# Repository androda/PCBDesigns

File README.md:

# PCBDesigns
 PCB Designs By Androda

 Note the Non-Commercial license.  You are encouraged to make these boards for yourself (personal use) or as gifts for others (provided that they are true gifts, and not being used to trade for something).  If you would like to license these designs for commercial sale, please contact me and we can work out a license agreement: https://androda.work/about/

# BlueSCSI
 These PCBs are intended to be used with the BlueSCSI project, found here: https://github.com/erichelgeson/BlueSCSI

# Newton
 PCBs for the Apple Newton

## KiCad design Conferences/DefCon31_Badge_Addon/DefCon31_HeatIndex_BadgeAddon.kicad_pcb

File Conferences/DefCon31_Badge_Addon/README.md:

# DefCon 31 Badge Addon
 This was my quick attempt to get something ready for DefCon 31.  The process of getting the PCB outline imported to KiCAD was not easy.

# What does it do?
 It's a "[Heat Index](https://www.weather.gov/safety/heat-index)" calculator and indicator.  The Heat Index is a way to calculate the temperature it "feels like" based on the combination of temperature and humidity in your current environment.
 
 The LED flashes about once per second (internal oscillators being as they are), with a color based on the calculated Heat Index.  Note that these temperatures are all in Fahrenheit.  Blue for < 80 degrees, Green for 81 to 90 degrees, Yellow for 91 to 104 degrees, Red for 105 to 125 degrees, and Purple for anything above that.

 The "yellow" color doesn't work very well due to lack of time in figuring out good PWM mixing values.  I use the term PWM loosely here, it's basically manual PWM due to issues with getting hardware PWM working properly
 
 Battery life isn't great, I was unable to get STOP mode with RTC wake working properly, even with a supposed "template" for doing so from the manufacturer.  Instead it uses SLEEP mode with a hardware timer wakeup, and the battery lasts about 12 hours.

 It's also a breakout board in that I routed all the additional pins to standard 2.54mm header strip positions.  So go ahead and reflash this as something more useful later on.  :)
 
# Is it useful?
 Kind of.  Maybe.  Was a good project for learning the [STM32Duino](https://github.com/stm32duino/Arduino_Core_STM32) framework, and for discovering that basically nothing in Arduino is as easy as it sounds when trying to use hardware peripherals.
 
# What chips are those?
* SHTC3 Temperature and Humidity Sensor
* STM32F030 Microcontroller
* Osram LRTBR48G LED
 
# License
 Licensed Creative Commons Attribution-NonCommercial-ShareAlike 4.0.
 https://creativecommons.org/licenses/by-nc-sa/4.0/
 https://creativecommons.org/licenses/by-nc-sa/4.0/deed.fr

Obligatory PCB Image:

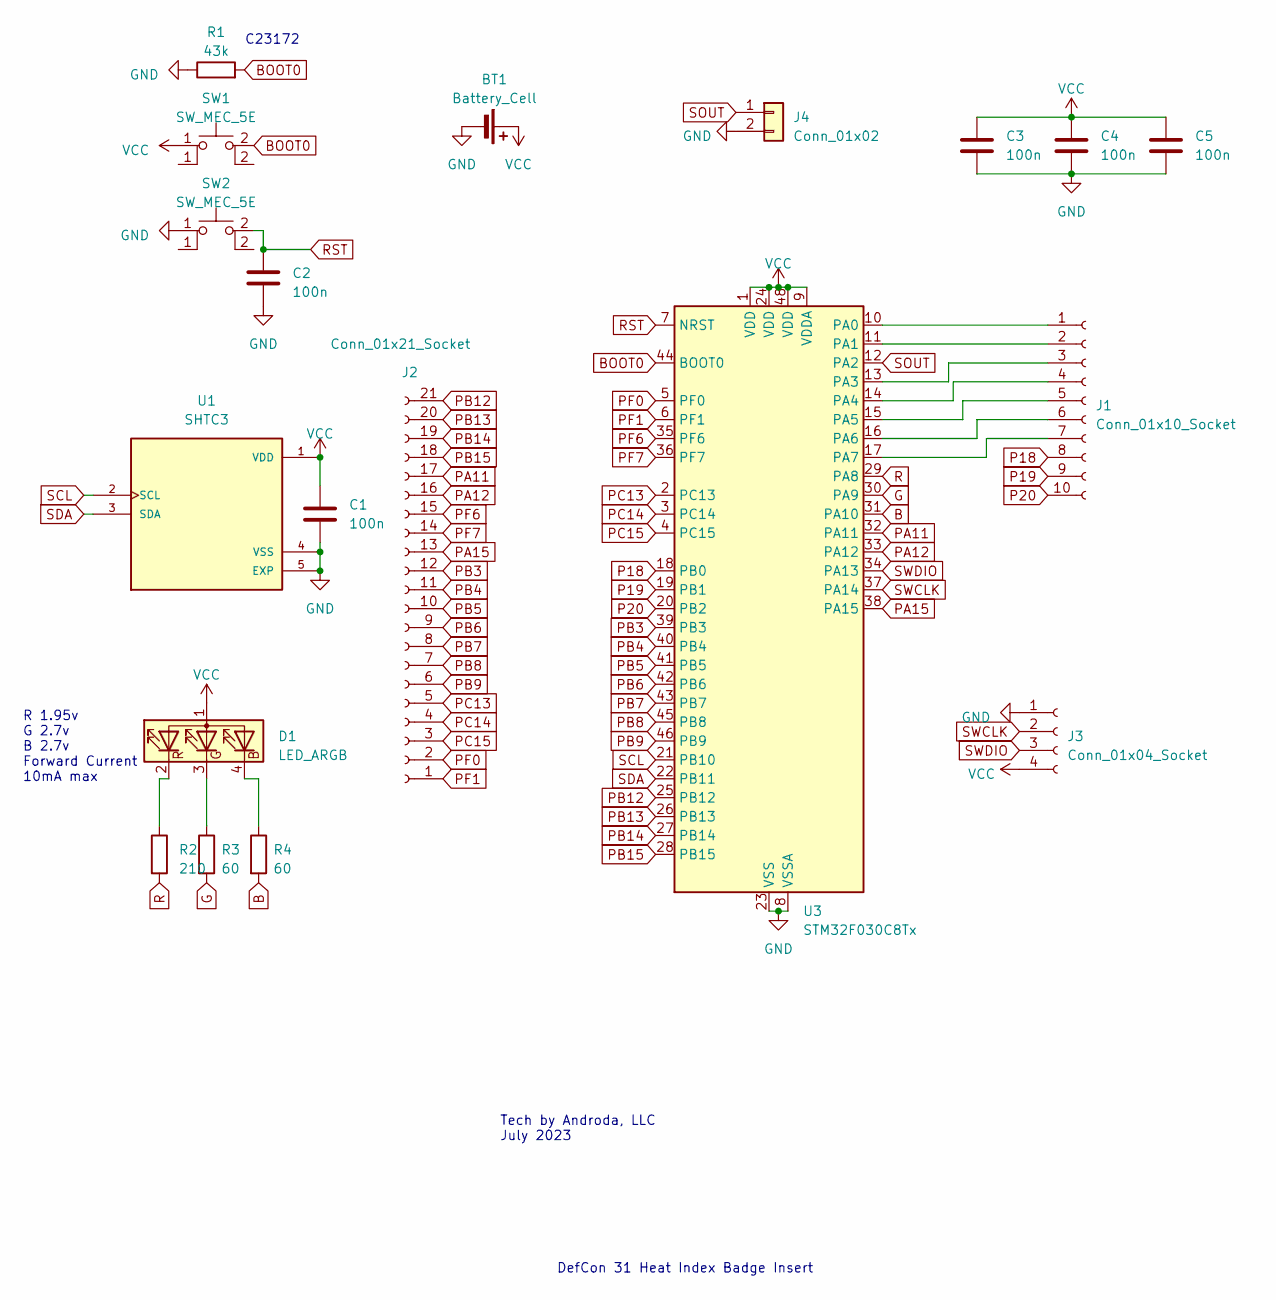
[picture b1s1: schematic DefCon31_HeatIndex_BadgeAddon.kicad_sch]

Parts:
BT1: Battery_Cell; CR1632
C1, C2, C3, C4, C5: 100n; C_0603_1608Metric
D1: LED_ARGB; LRTB_R48G
J1: Conn_01x10_Socket; PinSocket_1x10_P2.54mm_Vertical
J2: Conn_01x21_Socket; PinSocket_1x21_P2.54mm_Vertical
J3: Conn_01x04_Socket; PinSocket_1x04_P2.54mm_Vertical
J4: Conn_01x02; PinSocket_1x02_P2.54mm_Vertical
R1: 43k; R_0603_1608Metric
R2: 210; R_0603_1608Metric
R3, R4: 60; R_0603_1608Metric
SW1, SW2: SW_MEC_5E; TS-1187A-B-A-B
U1: SHTC3; SON100P200X200X80-5N; PARTREV 3
U3: STM32F030C8Tx; LQFP-48_7x7mm_P0.5mm

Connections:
B: R4.2, U3.31 (PA10)
BOOT0: R1.2, SW1.2, U3.44 (BOOT0)
G: R3.2, U3.30 (PA9)
GND: BT1.2 (-), C1.2, C2.2, C3.2, C4.2, C5.2, J3.1, J4.2, R1.1, SW2.1, U1.4 (VSS), U1.5 (EXP), U3.8 (VSSA), U3.23 (VSS), U3.47 (VSS)
unnamed: D1.4 (BK), R4.1
unnamed: D1.3 (GK), R3.1
unnamed: D1.2 (RK), R2.1
unnamed: J1.1, U3.10 (PA0)
unnamed: J1.2, U3.11 (PA1)
unnamed: J1.3, U3.13 (PA3)
unnamed: J1.4, U3.14 (PA4)
unnamed: J1.5, U3.15 (PA5)
unnamed: J1.6, U3.16 (PA6)
unnamed: J1.7, U3.17 (PA7)
P18: J1.8, U3.18 (PB0)
P19: J1.9, U3.19 (PB1)
P20: J1.10, U3.20 (PB2)
PA11: J2.17, U3.32 (PA11)
PA12: J2.16, U3.33 (PA12)
PA15: J2.13, U3.38 (PA15)
PB3: J2.12, U3.39 (PB3)
PB4: J2.11, U3.40 (PB4)
PB5: J2.10, U3.41 (PB5)
PB6: J2.9, U3.42 (PB6)
PB7: J2.8, U3.43 (PB7)
PB8: J2.7, U3.45 (PB8)
PB9: J2.6, U3.46 (PB9)
PB12: J2.21, U3.25 (PB12)
PB13: J2.20, U3.26 (PB13)
PB14: J2.19, U3.27 (PB14)
PB15: J2.18, U3.28 (PB15)
PC13: J2.5, U3.2 (PC13)
PC14: J2.4, U3.3 (PC14)
PC15: J2.3, U3.4 (PC15)
PF0: J2.2, U3.5 (PF0)
PF1: J2.1, U3.6 (PF1)
PF6: J2.15, U3.35 (PF6)
PF7: J2.14, U3.36 (PF7)
R: R2.2, U3.29 (PA8)
RST: C2.1, SW2.2, U3.7 (NRST)
SCL: U1.2 (SCL), U3.21 (PB10)
SDA: U1.3 (SDA), U3.22 (PB11)
SOUT: J4.1, U3.12 (PA2)
SWCLK: J3.2, U3.37 (PA14)
SWDIO: J3.3, U3.34 (PA13)
VCC: BT1.1 (+), C1.1, C3.1, C4.1, C5.1, D1.1 (A), J3.4, SW1.1, U1.1 (VDD), U3.1 (VDD), U3.9 (VDDA), U3.24 (VDD), U3.48 (VDD)

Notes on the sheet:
R 1.95v G 2.7v B 2.7v Forward Current 10mA max
DefCon 31 Heat Index Badge Insert
Tech by Androda, LLC July 2023
C23172

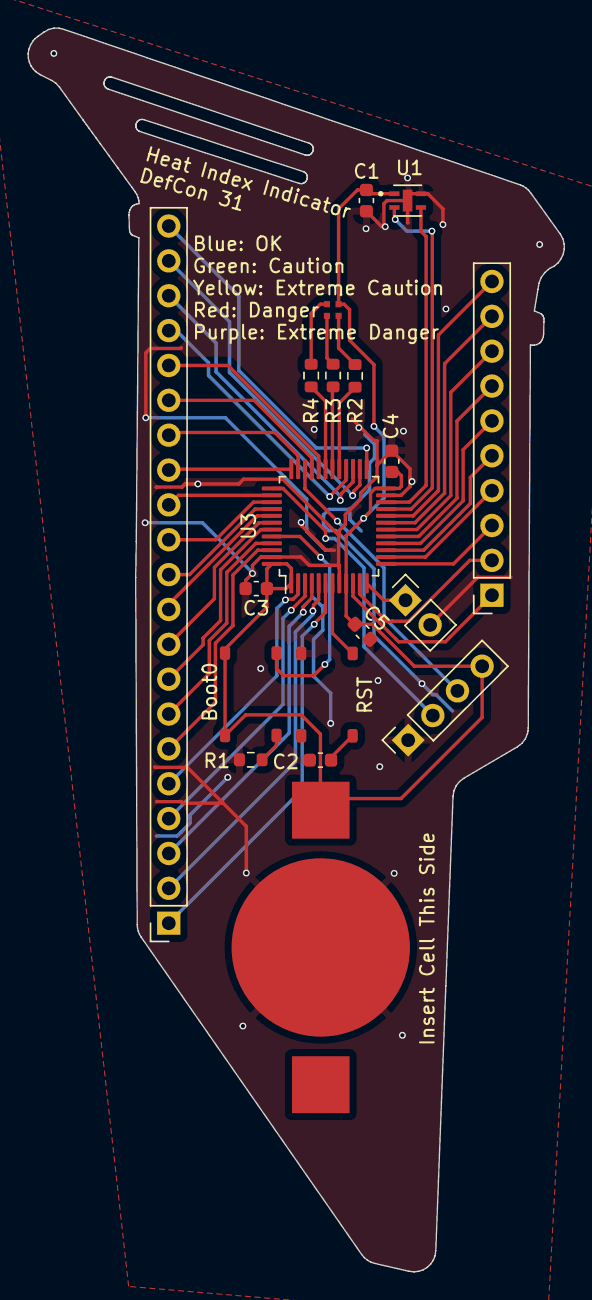
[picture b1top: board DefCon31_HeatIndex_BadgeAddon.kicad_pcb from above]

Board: 2 copper layers, 39.1 x 90.6 mm, 19 parts (0 on the bottom side), 46 nets.

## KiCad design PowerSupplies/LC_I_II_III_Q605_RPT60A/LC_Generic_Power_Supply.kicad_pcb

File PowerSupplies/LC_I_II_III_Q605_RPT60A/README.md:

Licensed Creative Commons Attribution-NonCommercial-ShareAlike 4.0.
https://creativecommons.org/licenses/by-nc-sa/4.0/
https://creativecommons.org/licenses/by-nc-sa/4.0/deed.fr

This is a power supply replacement design for the LC I through III series plus Q605.  It uses a MeanWell RPT-60A power supply that provides the usual 12/5/-5, with this PCB being effectively a protection board to try and keep your vintage system safe in case of power surges or regulation failures.  It's a working design, just move over the power output cable from the original supply (which could need extending).

This design uses the output pads layout from the "MacTX LC" which was released to the public domain.  Other than that it's an original design.

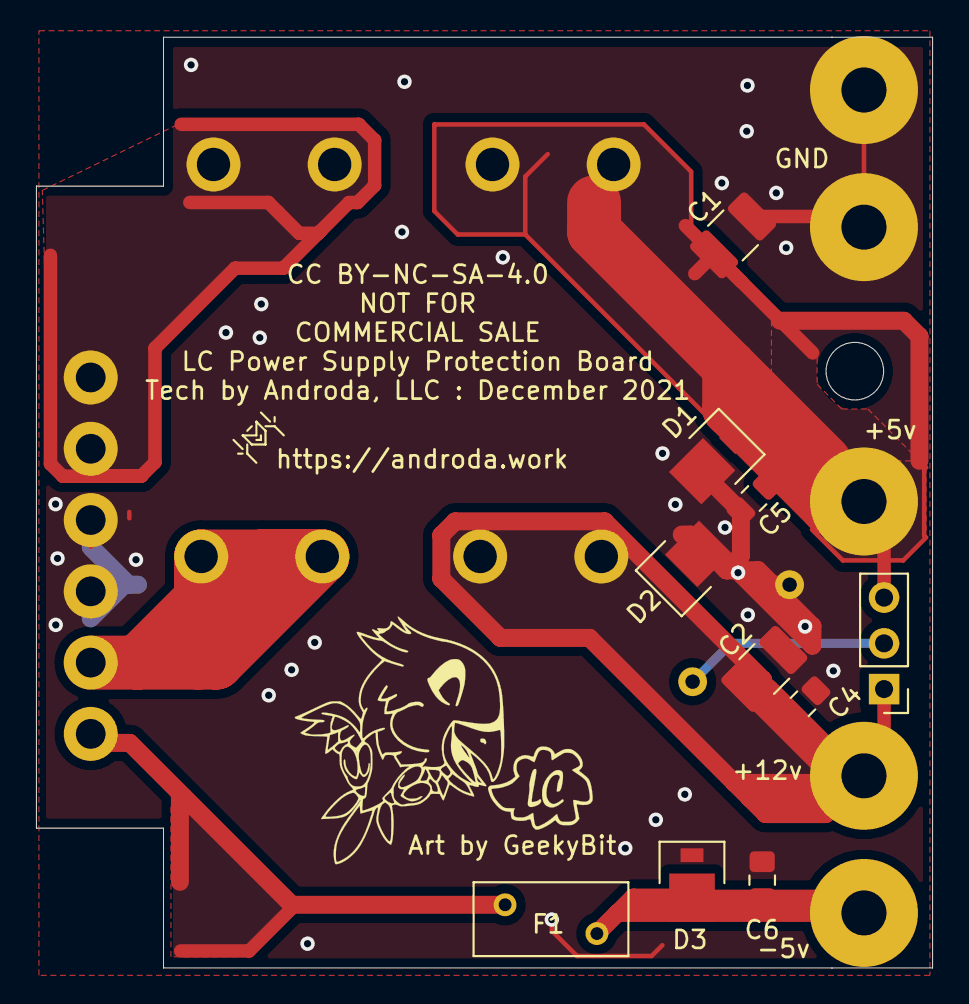
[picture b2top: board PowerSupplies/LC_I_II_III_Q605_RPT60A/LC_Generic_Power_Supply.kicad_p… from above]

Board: 2 copper layers, 49.8 x 51.7 mm, 17 parts (1 on the bottom side), 8 nets.

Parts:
C1, C2: 47uF 10v; C_1210_3225Metric_Pad1.42x2.65mm_HandSolder
C4, C5, C6: C; C_0805_2012Metric_Pad1.15x1.40mm_HandSolder
D1, D3: 5.6v Zener; DO-220AA
D2: 12.6v Zener; DO-220AA
F1: Polyfuse; Fuse_BelFuse_0ZRE0005FF_L8.3mm_W3.8mm
FH1, FH2: FuseHolders_FC-202-24
H2: MountingHole; MountingHole_3.2mm_M3
J1: RPT-60-6Pin-Out
J3: Conn_01x03_Male; PinHeader_1x03_P2.54mm_Vertical
J6: Conn_01x05_Male; LC_MACAA_Pads
R1: R; R_Axial_DIN0207_L6.3mm_D2.5mm_P7.62mm_Horizontal
Ref**: Val**; MACAAAAAAAAAA_1812

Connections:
+5V: C1.1, C5.1, D1.1, FH2.2, J3.3, J6.3
+12V: C2.1, C4.1, D2.1, FH1.2, J3.1, J6.4
-5V: C6.1, D3.2, F1.1, J6.5
GND: C1.2, C2.2, C4.2, C5.2, C6.2, D1.2, D2.2, D3.1, J1.3, J1.4, J6.1, J6.2, R1.2
unnamed: F1.2, J1.6
unnamed: FH1.1, J1.5
unnamed: FH2.1, J1.1, J1.2
unnamed: J3.2, R1.1

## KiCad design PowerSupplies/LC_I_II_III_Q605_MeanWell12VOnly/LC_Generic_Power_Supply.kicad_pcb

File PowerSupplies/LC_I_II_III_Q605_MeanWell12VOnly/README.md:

Licensed Creative Commons Attribution-NonCommercial-ShareAlike 4.0.
https://creativecommons.org/licenses/by-nc-sa/4.0/
https://creativecommons.org/licenses/by-nc-sa/4.0/deed.fr

This is a power supply replacement design for the LC I through III series plus Q605.  It uses a 12v MeanWell power supply which is then down-converted as necessary to provide the usual 12/5/-5 supply.  It's a working design, but too big of a pain to try and sell given the very small working area and cost which approaches a new old stock power supply replacement.  In the future when LC power supplies are entirely unavailble it might have some use.

This design uses the output pads layout from the "MacTX LC" which was released to the public domain.  Other than that it's an original design.

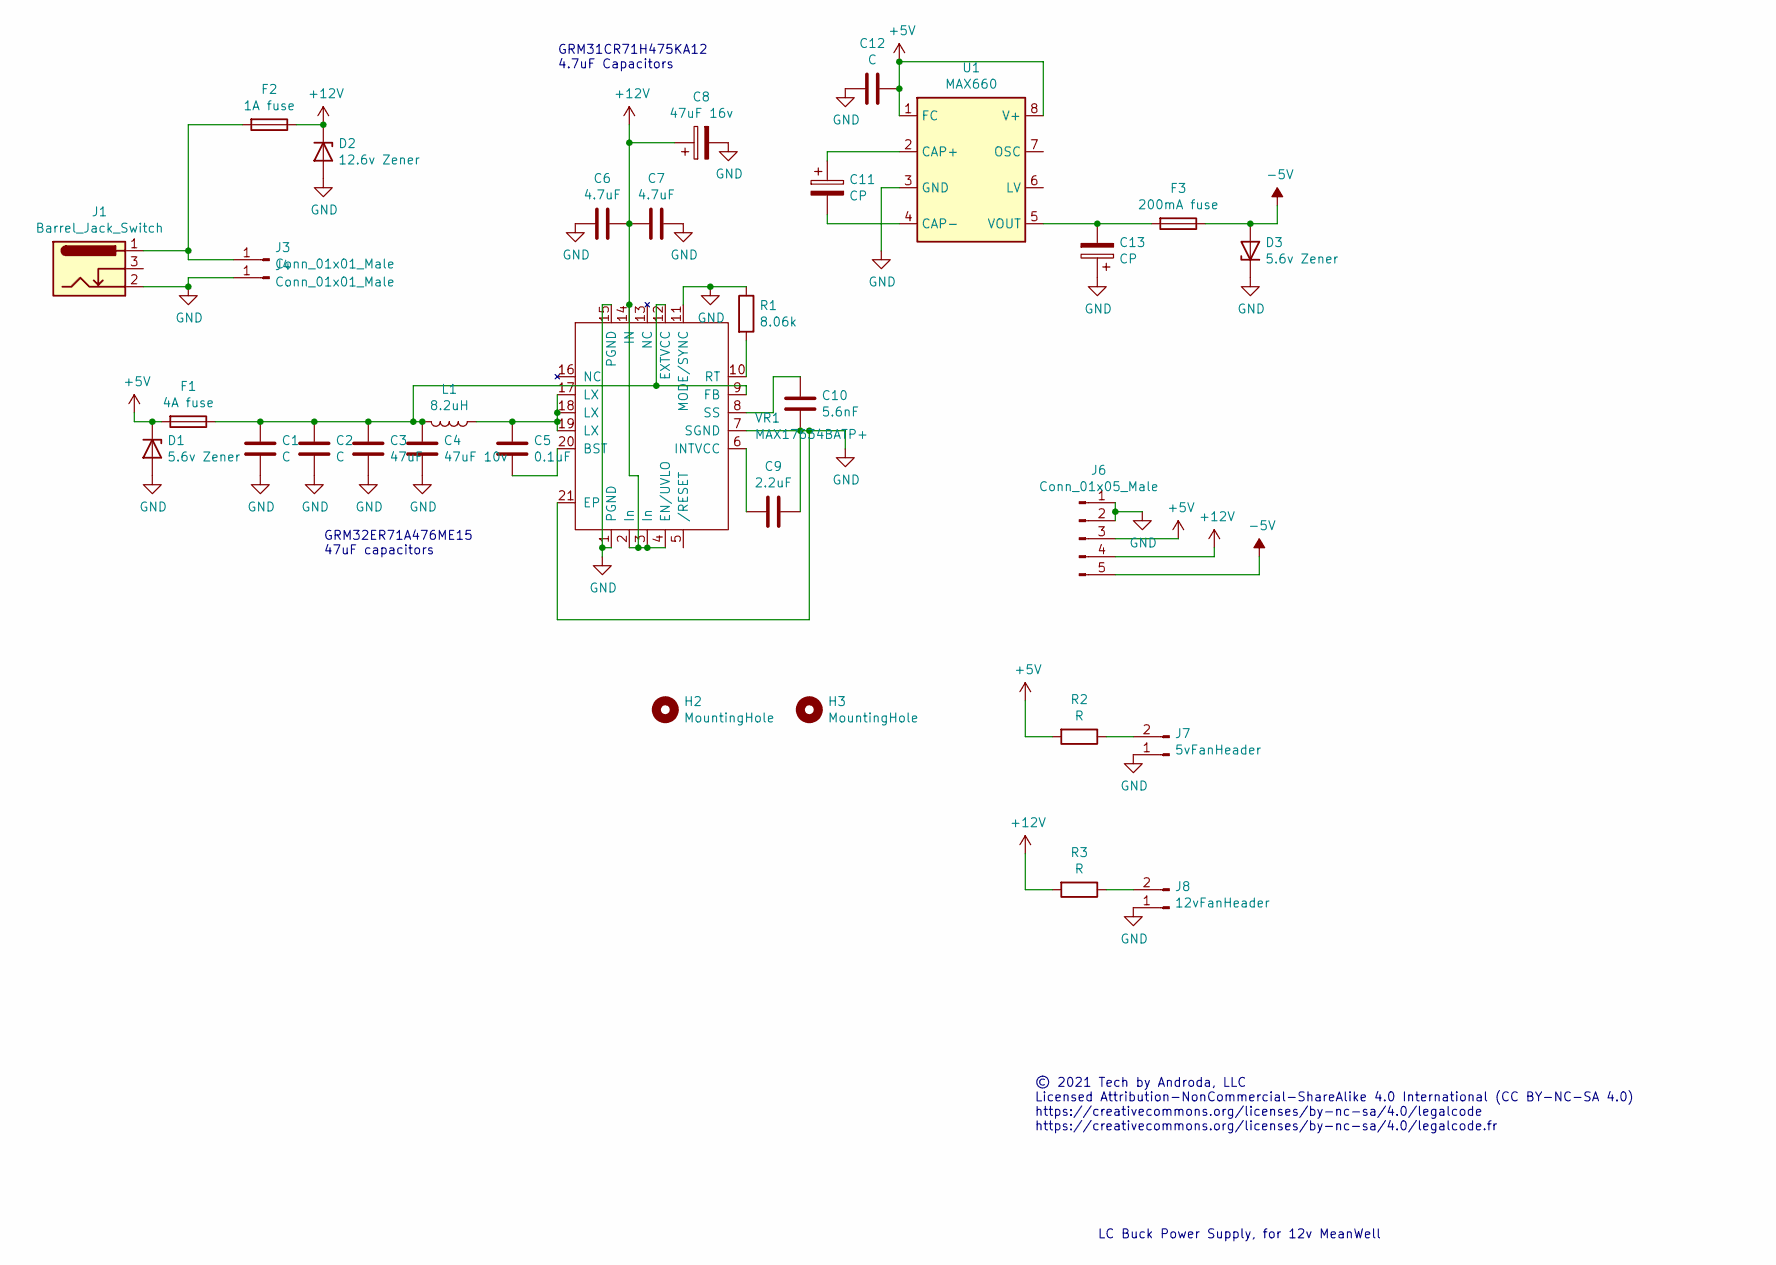
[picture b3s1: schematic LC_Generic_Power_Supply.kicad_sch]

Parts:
C1: C; C_0805_2012Metric_Pad1.15x1.40mm_HandSolder
C2: C; C_0603_1608Metric_Pad1.05x0.95mm_HandSolder
C3: 47uF; C_1210_3225Metric_Pad1.42x2.65mm_HandSolder
C4: 47uF 10v; C_1210_3225Metric_Pad1.42x2.65mm_HandSolder
C5: 0.1uF; C_0603_1608Metric
C6, C7: 4.7uF; C_1206_3216Metric_Pad1.42x1.75mm_HandSolder
C8: 47uF 16v; C_1206_3216Metric_Pad1.42x1.75mm_HandSolder
C9: 2.2uF; C_0603_1608Metric
C10: 5.6nF; C_0603_1608Metric
C11, C13: CP; C_0805_2012Metric_Pad1.15x1.40mm_HandSolder
C12: C; C_0603_1608Metric
D1, D3: 5.6v Zener; DO-220AA
D2: 12.6v Zener; DO-220AA
F1: 4A fuse; Fuse_Littelfuse-LVR100_NoOutline
F2: 1A fuse; Fuse_Littelfuse-LVR100_NoOutline
F3: 200mA fuse; Fuse_Littelfuse-LVR100_NoOutline
H2, H3: MountingHole; MountingHole_3.2mm_M3
J1: Barrel_Jack_Switch; RandomBasementBarrelJack
J3, J4: Conn_01x01_Male; MACAA_Individual_Pad
J6: Conn_01x05_Male; LC_MACAA_Pads
J7: 5vFanHeader; PinHeader_1x02_P2.54mm_Vertical
J8: 12vFanHeader; PinHeader_1x02_P2.54mm_Vertical
L1: 8.2uH; HM79M-60
R1: 8.06k; R_0805_2012Metric_Pad1.15x1.40mm_HandSolder
R2, R3: R; R_Axial_DIN0207_L6.3mm_D2.5mm_P7.62mm_Horizontal
U1: MAX660; SOIC-8_3.9x4.9mm_P1.27mm
VR1: MAX17634BATP+; QFN-20-1EP_4x4mm_P0.5mm_EP2.7x2.7mm

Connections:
+5V: C12.1, D1.1 (K), F1.2, J6.3, R2.2, U1.1 (FC), U1.8 (V+)
+12V: C6.1, C7.2, C8.1, D2.1 (K), F2.1, J6.4, R3.2, VR1.2 (In), VR1.3 (In), VR1.4 (EN/UVLO), VR1.14 (IN)
-5V: D3.2 (A), F3.1, J6.5
GND: C1.2, C2.2, C3.2, C4.2, C6.2, C7.1, C8.2, C9.2, C10.2, C12.2, C13.1, D1.2 (A), D2.2 (A), D3.1 (K), J1.2, J4.1, J6.1, J6.2, J7.1, J8.1, R1.1, U1.3 (GND), VR1.1 (PGND), VR1.7 (SGND), VR1.11 (MODE/SYNC), VR1.15 (PGND), VR1.21 (EP)
unnamed: C1.1, C2.1, C3.1, C4.1, F1.1, L1.2, VR1.9 (FB), VR1.12 (EXTVCC)
unnamed: C5.1, VR1.20 (BST)
unnamed: C5.2, L1.1, VR1.17 (LX), VR1.18 (LX), VR1.19 (LX)
unnamed: C9.1, VR1.6 (INTVCC)
unnamed: C10.1, VR1.8 (SS)
unnamed: C11.1, U1.2 (CAP+)
unnamed: C11.2, U1.4 (CAP-)
unnamed: C13.2, F3.2, U1.5 (VOUT)
unnamed: F2.2, J1.1, J3.1
unnamed: J7.2, R2.1
unnamed: J8.2, R3.1
unnamed: R1.2, VR1.10 (RT)

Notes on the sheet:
© 2021 Tech by Androda, LLC Licensed Attribution-NonCommercial-ShareAlike 4.0 International (CC BY-NC-SA 4.0) https://creativecommons.org/licenses/by-nc-sa/4.0/legalcode https://creativecommons.org/licenses/by-nc-sa/4.0/legalcode.fr
GRM32ER71A476ME15 47uF capacitors
LC Buck Power Supply, for 12v MeanWell
GRM31CR71H475KA12 4.7uF Capacitors

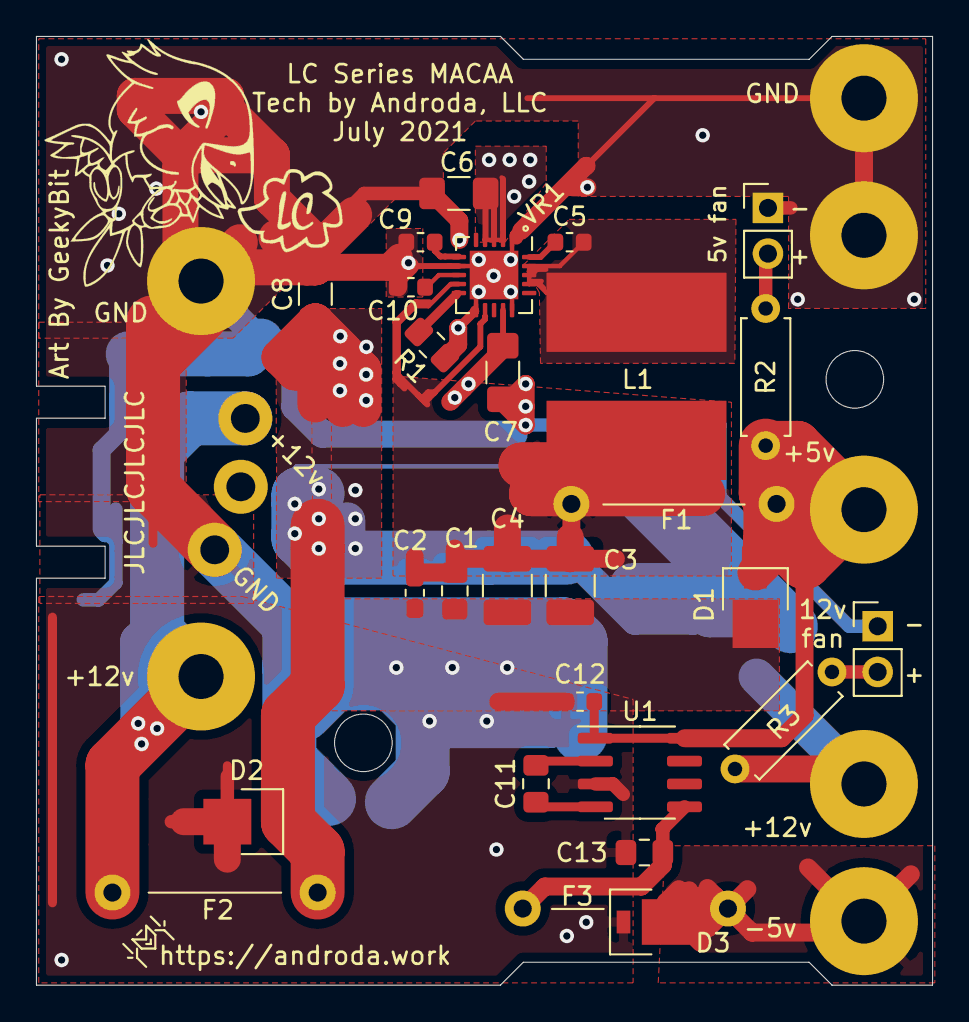
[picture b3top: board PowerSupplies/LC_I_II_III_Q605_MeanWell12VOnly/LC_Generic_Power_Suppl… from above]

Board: 2 copper layers, 49.8 x 52.7 mm, 34 parts (0 on the bottom side), 16 nets.

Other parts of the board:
Ref**: Val**; MACAAAAAAAAAA_1812

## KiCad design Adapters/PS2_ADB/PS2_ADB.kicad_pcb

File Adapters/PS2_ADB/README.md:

PS/2 Keyboard and Mouse to ADB adapter

This PCB is licensed Creative Commons Attribution-NonCommercial-ShareAlike 4.0.  https://creativecommons.org/licenses/by-nc-sa/4.0/ 

Software is licensed GPLV3 from Tashtari/lampmerchant: https://github.com/lampmerchant/tashtrio

# Programming
You'll need something like a PicKit3 to program the PIC12F1840.  The MPLab Snap did not work for me at all, for unknown reasons.

# Usage
Plug in your favorite PS/2 keyboard and mouse (to the correct ports plese, see silkscreen label), plug in the ADB connector to your Mac, and you're done.

# Compatibility
The V1 design was tested on my Beige G3 and works fine.

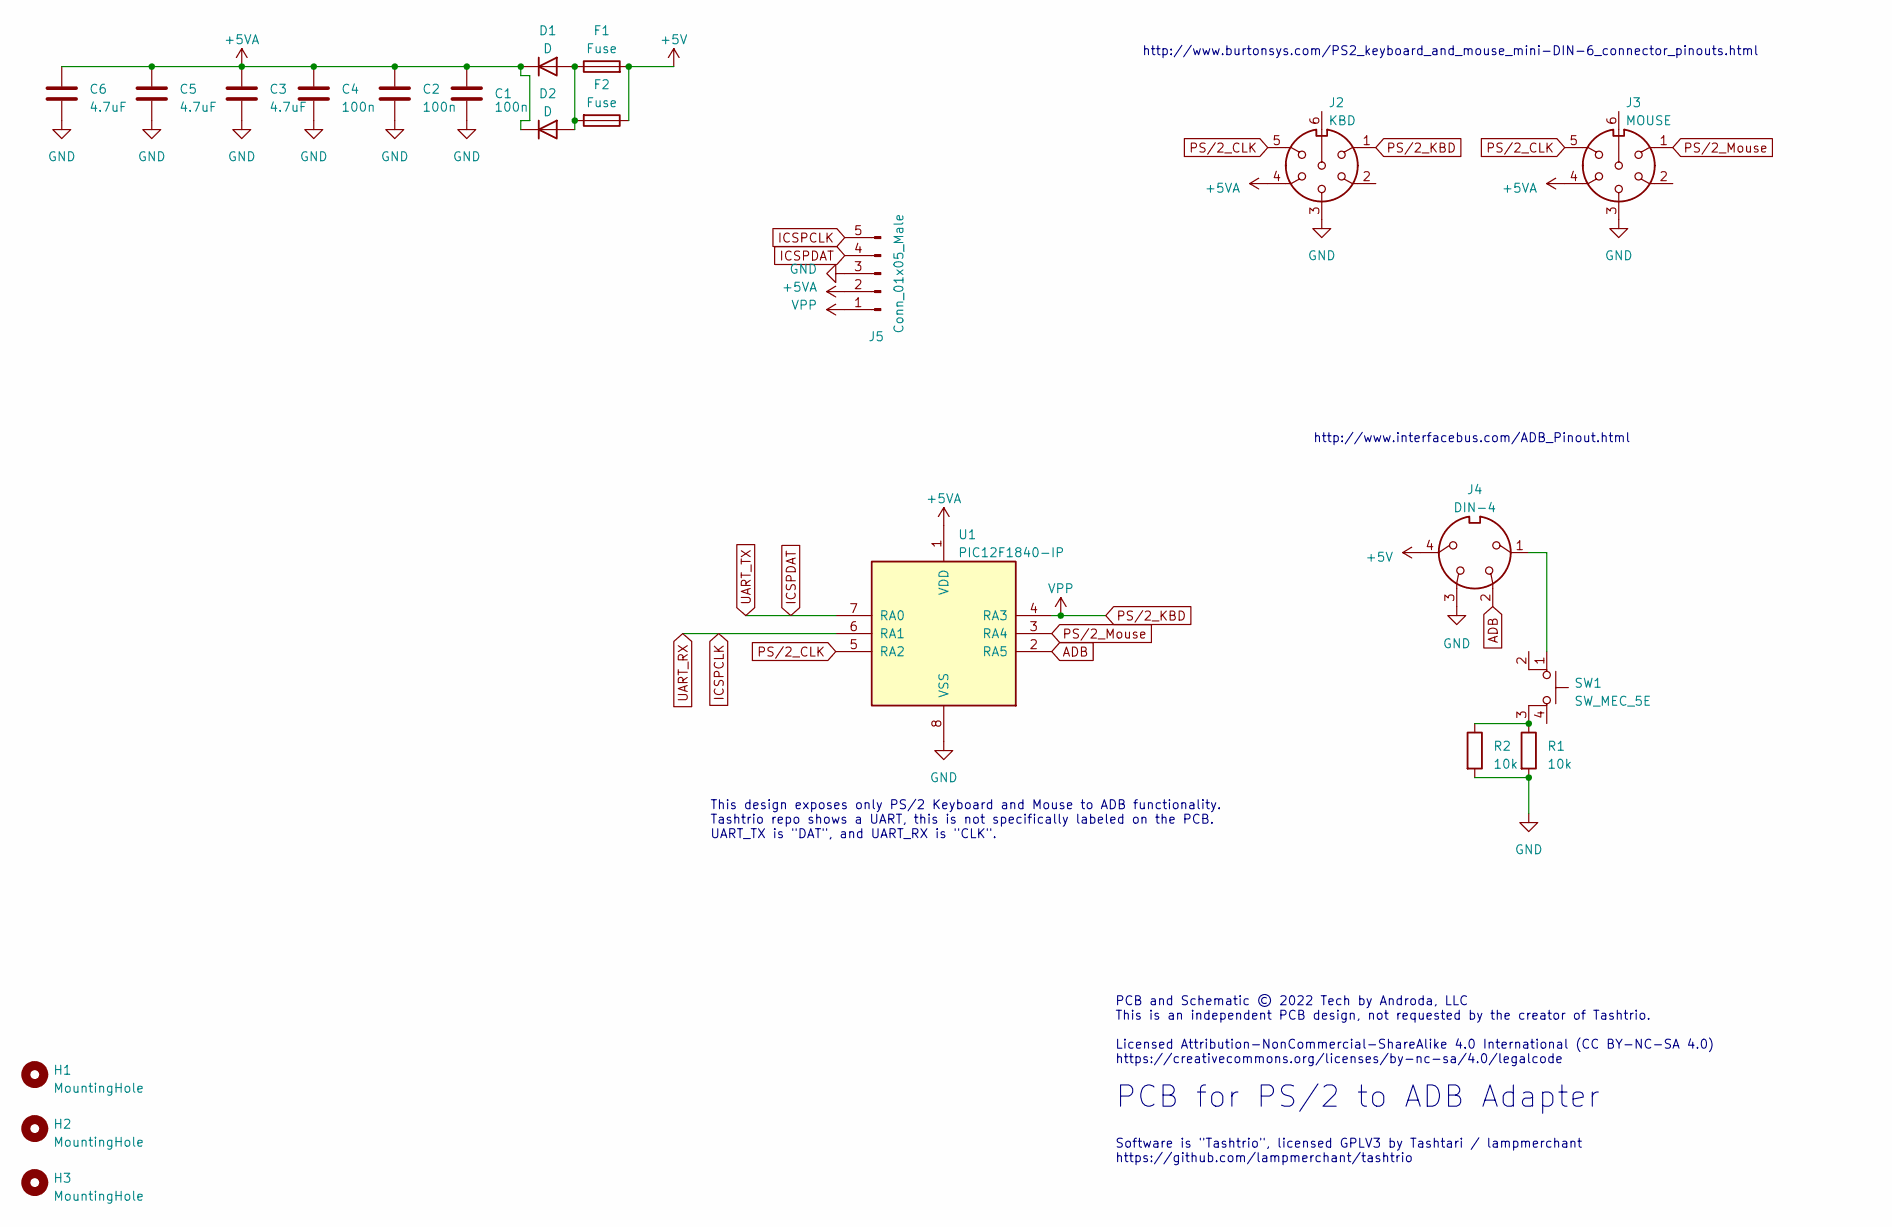
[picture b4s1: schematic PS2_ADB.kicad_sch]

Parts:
C1, C2, C4: 100n; C_0805_2012Metric_Pad1.18x1.45mm_HandSolder
C3: 4.7uF; CP_Radial_D6.3mm_P2.50mm
C5, C6: 4.7uF; CP_Radial_D5.0mm_P2.50mm
D1: D; D_DO-15_P12.70mm_Horizontal
D2: D; D_SMA
F1: Fuse; Fuse_0805_2012Metric_Pad1.15x1.40mm_HandSolder
F2: Fuse; Fuse_BelFuse_0ZRE0005FF_L8.3mm_W3.8mm
H1, H2, H3: MountingHole; MountingHole_3.2mm_M3
J2: KBD; PS2_MDR6_MINI-DIN
J3: MOUSE; PS2_MDR6_MINI-DIN
J4: DIN-4; ADB_MDR4_MINI-DIN
J5: Conn_01x05_Male; PinHeader_1x05_P2.54mm_Vertical
R1: 10k; R_0805_2012Metric_Pad1.20x1.40mm_HandSolder
R2: 10k; R_Axial_DIN0411_L9.9mm_D3.6mm_P12.70mm_Horizontal
SW1: SW_MEC_5E; SW_SPST_TL3305A
U1: PIC12F1840-IP; DIP-8_W7.62mm

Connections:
+5V: F1.2, F2.1, J4.4
+5VA: C1.1, C2.1, C3.1, C4.1, C5.1, C6.1, D1.1 (K), D2.1 (K), J2.4, J3.4, J5.2, U1.1 (VDD)
ADB: J4.2, U1.2 (RA5)
GND: C1.2, C2.2, C3.2, C4.2, C5.2, C6.2, J2.3, J3.3, J4.3, J5.3, R1.2, R2.2, U1.8 (VSS)
ICSPCLK: J5.5, U1.6 (RA1)
ICSPDAT: J5.4, U1.7 (RA0)
unnamed: D1.2 (A), D2.2 (A), F1.1, F2.2
unnamed: J4.1, SW1.1
unnamed: R1.1, R2.1, SW1.3 (K)
PS/2_CLK: J2.5, J3.5, U1.5 (RA2)
PS/2_KBD: J2.1, J5.1, U1.4 (RA3)
PS/2_Mouse: J3.1, U1.3 (RA4)

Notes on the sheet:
http://www.interfacebus.com/ADB_Pinout.html
This design exposes only PS/2 Keyboard and Mouse to ADB functionality. Tashtrio repo shows a UART, this is not specifically labeled on the PCB. UART_TX is "DAT", and UART_RX is "CLK".
PCB for PS/2 to ADB Adapter
Software is "Tashtrio", licensed GPLV3 by Tashtari / lampmerchant https://github.com/lampmerchant/tashtrio
http://www.burtonsys.com/PS2_keyboard_and_mouse_mini-DIN-6_connector_pinouts.html
PCB and Schematic © 2022 Tech by Androda, LLC This is an independent PCB design, not requested by the creator of Tashtrio. Licensed Attribution-NonCommercial-ShareAlike 4.0 International (CC BY-NC-SA 4.0) https://creativecommons.org/licenses/by-nc-sa/4.0/legalcode

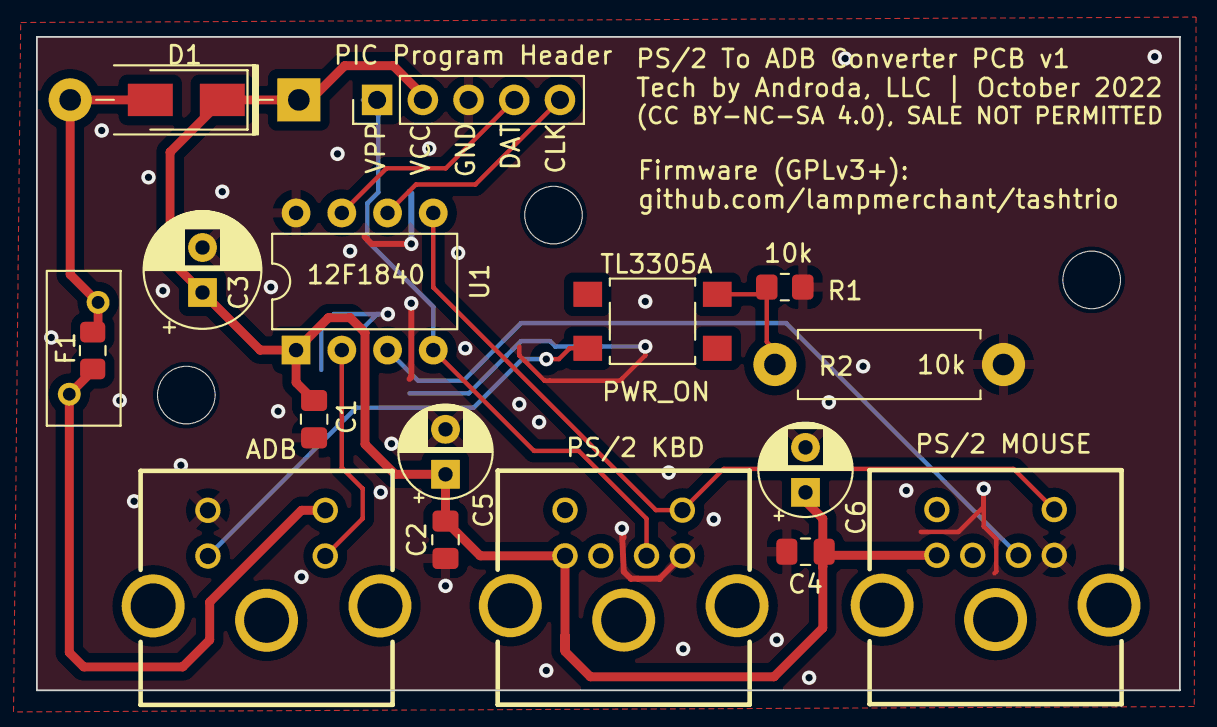
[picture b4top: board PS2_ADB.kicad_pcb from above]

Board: 2 copper layers, 63.5 x 36.3 mm, 21 parts (0 on the bottom side), 12 nets.

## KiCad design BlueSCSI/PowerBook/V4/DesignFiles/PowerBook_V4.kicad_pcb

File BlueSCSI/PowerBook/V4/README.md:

PowerBook BlueSCSI Version 4 [F1.TbA.PB.V4]
Designed by: Tech by Androda, LLC

Big Changes:
* All surface-mount components
* No jumpers!  The dual diode means logic or motor power will power the device with no selection necessary.
* Termination enable jumper is removed as well, because PowerBooks need termination 'always-on'
* Back to discrete resistors plus voltage regulator.  The termination ICs used on the previous V3 design were very hard to reliably get working first try, likely due to invisible corrosion from sitting in a warehouse for decades.  I could get them to work with some individual pin rework after the first round of soldering, but it was taking a very long time.

Tested on:
* PowerBook 180, boots 7.5.3 rascsi image
* PowerBook 540, boots 7.5.3 rascsi image

This design is *specifically for PowerBooks*.  Termination power *cannot be disabled* and this design is incompatible with any system where the hard drive is required to not terminate the bus.

If you need a version which allows termination to be disabled, try V3.

Height clearance is probably not an issue now that the mounting bracket is flush with the bottom of the PCB.

Note the 'USB Here' silkscreen, the USB port on the blue pill goes on that end.  The other way to say it is that the programming headers on the blue pill are on the same end as the 40 pin hard drive connector.

Mounting screws are M3.  With standard 1.6mm PCB thickness, the screws I use stick out about 1mm, and the mounting bracket is that thick to try and keep screws from sticking out the bottom.

Sleep Mode is untested.  Use at your own risk.

Notes on assembly:
Getting the SMD 40-pin connector to sit nicely and work properly is kind of hard.  Note that the black plastic part of the connector just barely overhangs the end of the PCB.  Place a scrap PCB of the same thickness underneath that tiny overhang before you hot air solder the connector into place.  This way it won't tip when hit with airflow.

On the two 20-pin rows, I suggest sticking the pins through the blue pill's header rows to align them properly.  Then set down on the PCB and solder just the ends.  That will ensure the rows are aligned and hold them in place for whatever solering technique you prefer.  Hot air tends to melt the plastic on these, so manual soldering may be most reliable.

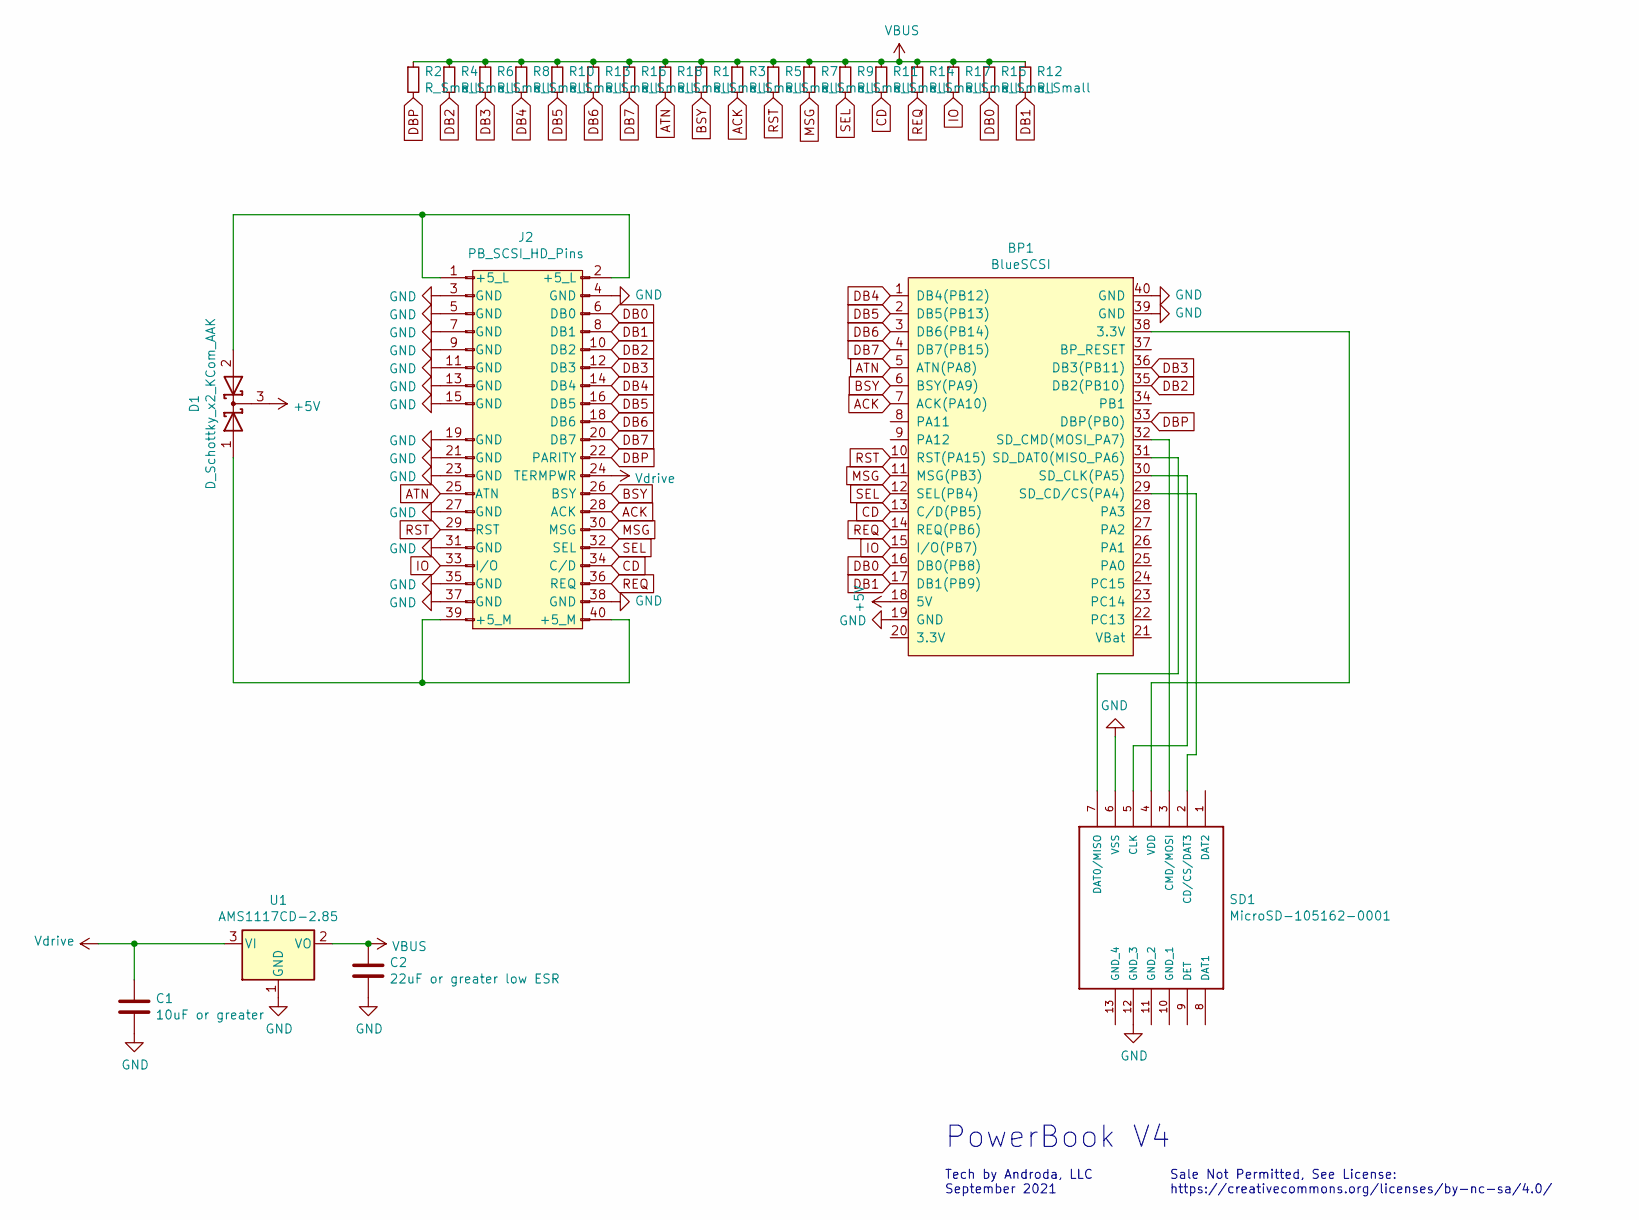
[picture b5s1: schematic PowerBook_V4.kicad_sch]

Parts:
BP1: BlueSCSI; SMDBluePill_rightLeg1
C1: 10uF or greater; C_1206_3216Metric
C2: 22uF or greater low ESR; C_1206_3216Metric
D1: D_Schottky_x2_KCom_AAK; SOT1061
J2: PB_SCSI_HD_Pins; PowerBook_BlueSCSI_SMD_Headers
R1, R2, R3, R4, R5, R6, R7, R8, R9, R10, R11, R12, R13, R14, R15, R16, R17, R18: R_Small; R_0603_1608Metric_Pad1.05x0.95mm_HandSolder
SD1: MicroSD-105162-0001; microsd_molex_1051620001; MANUFACTURER_PART_NUMBER 105162-0001; MOUSER_PART_NUMBER 538-105162-0001
U1: AMS1117CD-2.85; TO-252-3_TabPin2

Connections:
+5V: BP1.18 (5V), D1.3 (K)
ACK: BP1.7 (ACK(PA10)), J2.28 (ACK), R3.2
ATN: BP1.5 (ATN(PA8)), J2.25 (ATN), R18.2
BSY: BP1.6 (BSY(PA9)), J2.26 (BSY), R1.2
CD: BP1.13 (C/D(PB5)), J2.34 (C/D), R11.2
DB0: BP1.16 (DB0(PB8)), J2.6 (DB0), R15.2
DB1: BP1.17 (DB1(PB9)), J2.8 (DB1), R12.2
DB2: BP1.35 (DB2(PB10)), J2.10 (DB2), R4.2
DB3: BP1.36 (DB3(PB11)), J2.12 (DB3), R6.2
DB4: BP1.1 (DB4(PB12)), J2.14 (DB4), R8.2
DB5: BP1.2 (DB5(PB13)), J2.16 (DB5), R10.2
DB6: BP1.3 (DB6(PB14)), J2.18 (DB6), R13.2
DB7: BP1.4 (DB7(PB15)), J2.20 (DB7), R16.2
DBP: BP1.33 (DBP(PB0)), J2.22 (PARITY), R2.2
GND: BP1.19 (GND), BP1.39 (GND), BP1.40 (GND), C1.2, C2.2, J2.3 (GND), J2.4 (GND), J2.5 (GND), J2.7 (GND), J2.9 (GND), J2.11 (GND), J2.13 (GND), J2.15 (GND), J2.19 (GND), J2.21 (GND), J2.23 (GND), J2.27 (GND), J2.31 (GND), J2.35 (GND), J2.37 (GND), J2.38 (GND), SD1.6 (VSS), SD1.12 (GND_3), U1.1 (GND)
IO: BP1.15 (I/O(PB7)), J2.33 (I/O), R17.2
MSG: BP1.11 (MSG(PB3)), J2.30 (MSG), R7.2
unnamed: BP1.29 (SD_CD/CS(PA4)), SD1.2 (CD/CS/DAT3)
unnamed: BP1.30 (SD_CLK(PA5)), SD1.5 (CLK)
unnamed: BP1.31 (SD_DAT0(MISO_PA6)), SD1.7 (DAT0/MISO)
unnamed: BP1.32 (SD_CMD(MOSI_PA7)), SD1.3 (CMD/MOSI)
unnamed: BP1.38 (3.3V), SD1.4 (VDD)
unnamed: D1.1 (A), J2.39 (+5_M), J2.40 (+5_M)
unnamed: D1.2 (A), J2.1 (+5_L), J2.2 (+5_L)
REQ: BP1.14 (REQ(PB6)), J2.36 (REQ), R14.2
RST: BP1.10 (RST(PA15)), J2.29 (RST), R5.2
SEL: BP1.12 (SEL(PB4)), J2.32 (SEL), R9.2
VBUS: C2.1, R1.1, R2.1, R3.1, R4.1, R5.1, R6.1, R7.1, R8.1, R9.1, R10.1, R11.1, R12.1, R13.1, R14.1, R15.1, R16.1, R17.1, R18.1, U1.2 (VO)
Vdrive: C1.1, J2.24 (TERMPWR), U1.3 (VI)

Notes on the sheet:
PowerBook V4
Sale Not Permitted, See License: https://creativecommons.org/licenses/by-nc-sa/4.0/
Tech by Androda, LLC September 2021

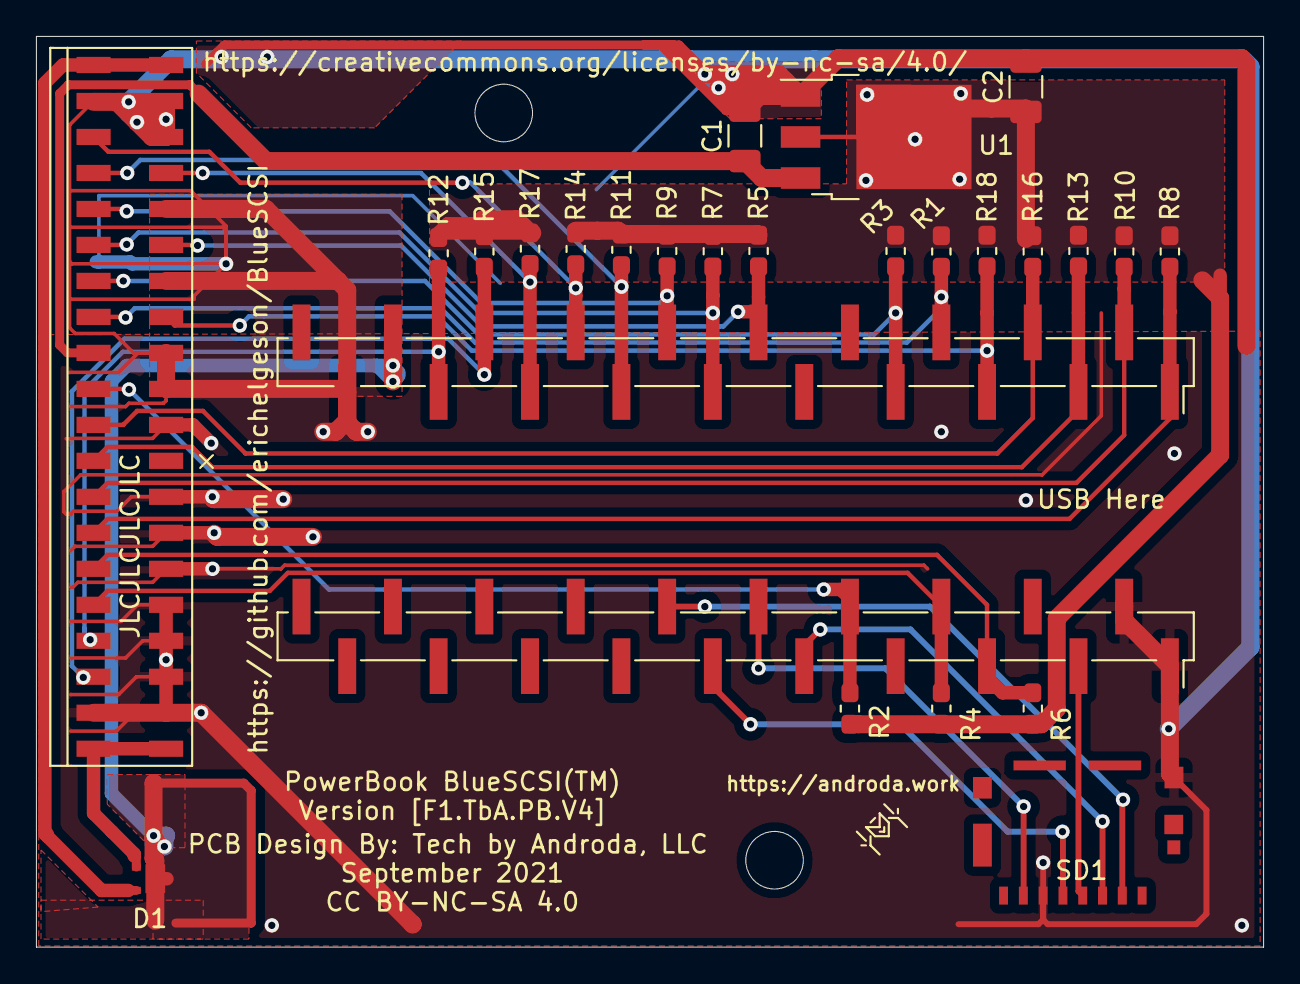
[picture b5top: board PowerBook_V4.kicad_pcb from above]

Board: 2 copper layers, 68.2 x 50.6 mm, 25 parts (0 on the bottom side), 29 nets.

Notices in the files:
Adapters/PS2_ADB/PS2_ADB.kicad_pcb:
(CC BY-NC-SA 4.0), SALE NOT PERMITTED
Firmware (GPLv3+):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
BlueSCSI/Desktop/F1.XCVR.TbA.D.V1/XCVR_F1_SMD_V1.kicad_pcb:
© Tech by Androda, LLC
